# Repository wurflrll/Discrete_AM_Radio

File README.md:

# Discrete AM Radio

## 27MHz AM Radio from Discrete Components

# Descriptions
This project comprises two different PCBs, a Receiver and Transmitter.  The circuits rely on basic BJT amplifier designs, a 27MHz oscillator.

## Added Files
This contains all the files from my two KiCad project and the BOMS (factory assembled unlike Sawtooth generator project).

## Problems
Crystal Oscillator has issues because the loop gain is too high, due to a mispredicted Q factor of
the crystal.

Trying to use a simple op-amp circuit for the preamplification of the microphone signal was a bad idea.  
The NCS20072D is simply too high noise, especially for a high gain pre-amp from a ~-50dB microphone.

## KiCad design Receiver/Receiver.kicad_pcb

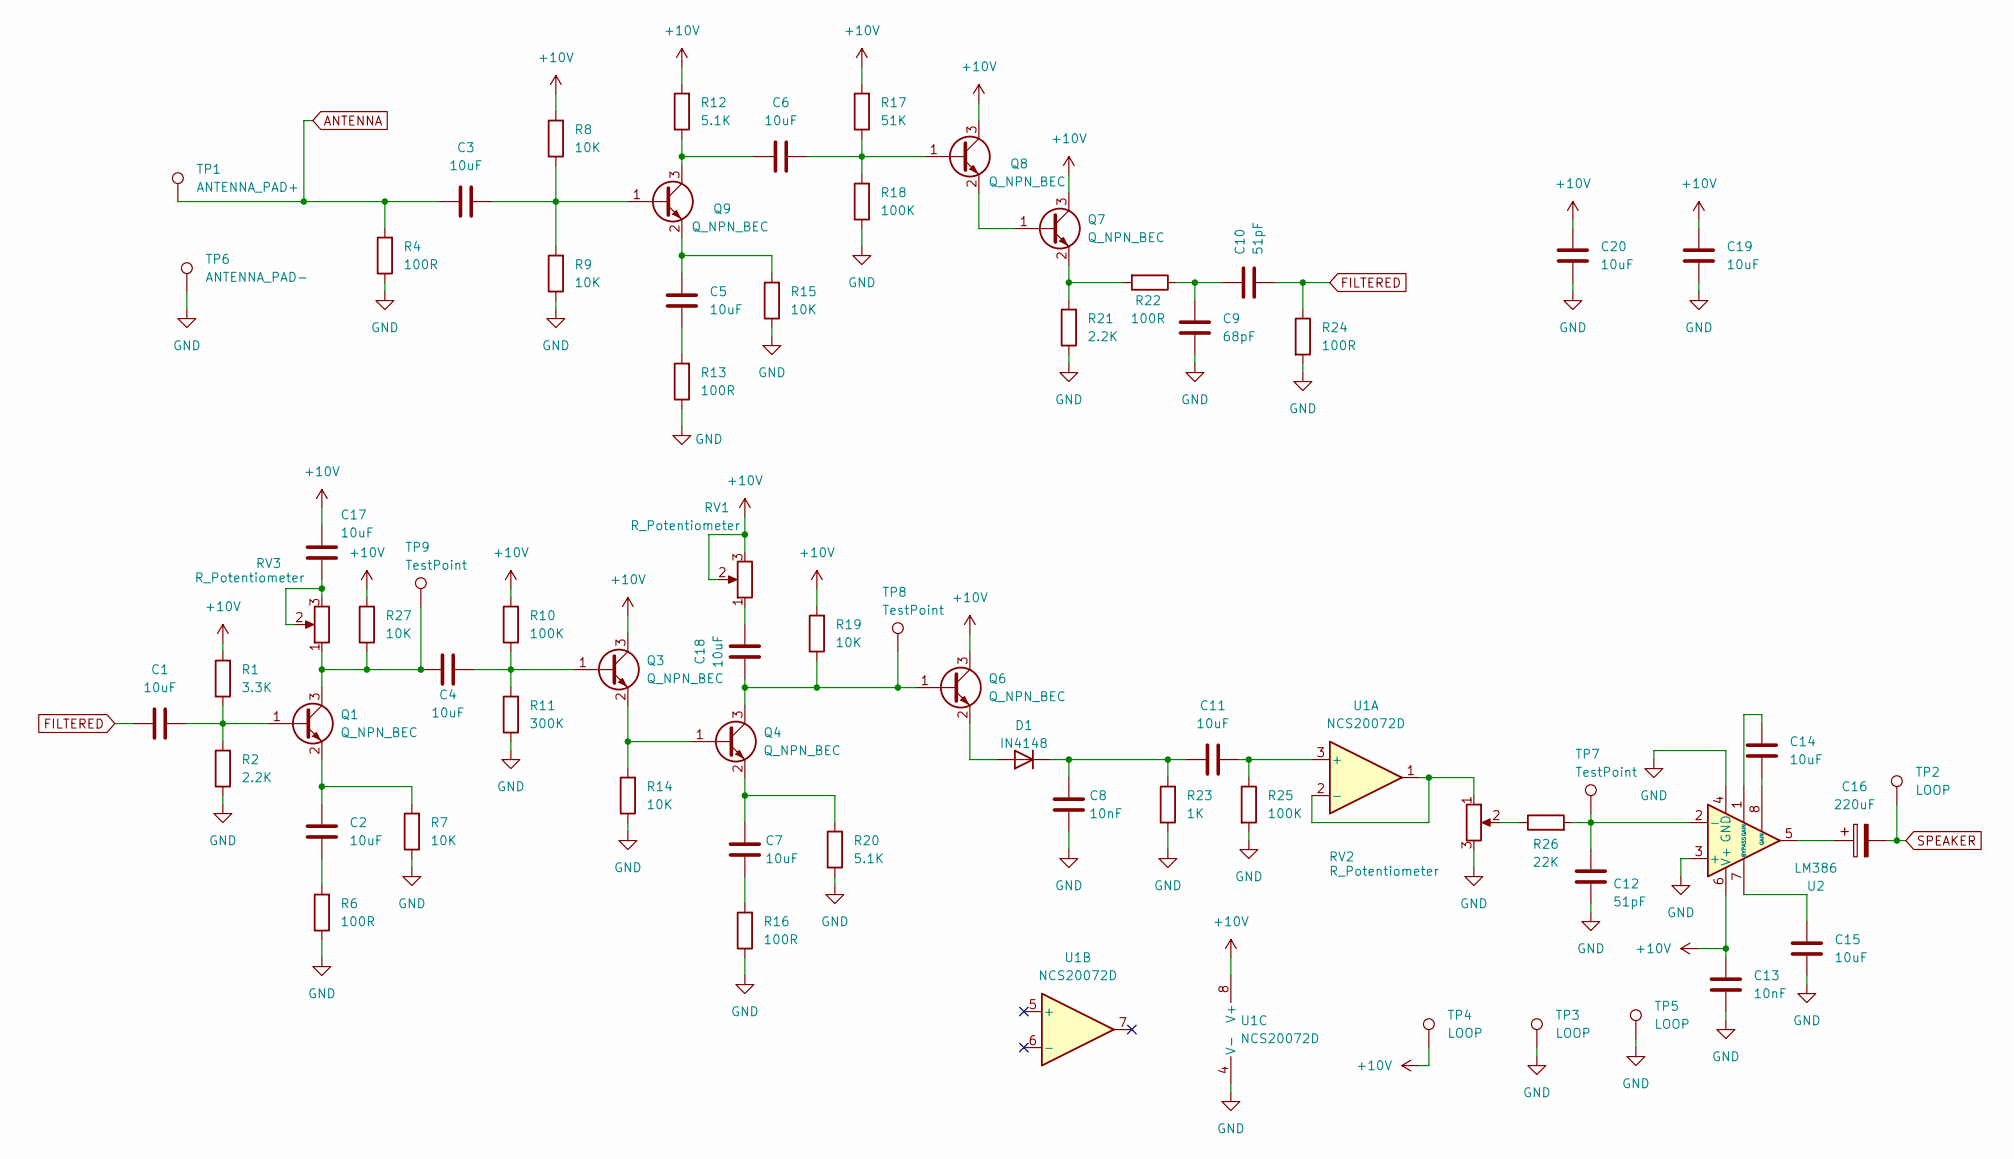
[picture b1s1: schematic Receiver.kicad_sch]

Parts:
C1, C2, C3, C4, C5, C6, C7, C11, C14, C15, C17, C18, C19, C20: 10uF; C_0603_1608Metric
C8, C13: 10nF; C_0603_1608Metric
C9: 68pF; C_0603_1608Metric
C10, C12: 51pF; C_0603_1608Metric
C16: 220uF; C_Radial_D8.0mm_H11.5mm_P3.50mm
D1: IN4148; D_SOD-123
Q1, Q3, Q4, Q6, Q7, Q8, Q9: Q_NPN_BEC; SOT-23
R1: 3.3K; R_0603_1608Metric
R2, R21: 2.2K; R_0603_1608Metric
R4, R6, R13, R16, R22, R24: 100R; R_0603_1608Metric
R7, R8, R9, R14, R15, R19, R27: 10K; R_0603_1608Metric
R10, R18, R25: 100K; R_0603_1608Metric
R11: 300K; R_0603_1608Metric
R12, R20: 5.1K; R_0603_1608Metric
R17: 51K; R_0603_1608Metric
R23: 1K; R_0603_1608Metric
R26: 22K; R_0603_1608Metric
RV1, RV2, RV3: R_Potentiometer; Potentiometer_Bourns_3386P_Vertical
TP1: ANTENNA_PAD+; TestPoint_Pad_D4.0mm
TP2, TP3, TP4, TP5: LOOP; TestPoint_Loop_D2.50mm_Drill1.0mm
TP6: ANTENNA_PAD-; TestPoint_Pad_D4.0mm
TP7, TP8, TP9: TestPoint; TestPoint_Plated_Hole_D2.0mm
U1: NCS20072D; SOIC-8_3.9x4.9mm_P1.27mm
U2: LM386; SOIC-8_3.9x4.9mm_P1.27mm

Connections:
+10V: C13.1, C17.2, C19.2, C20.2, Q3.3 (C), Q6.3 (C), Q7.3 (C), Q8.3 (C), R1.2, R8.2, R10.2, R12.2, R17.2, R19.2, R27.2, RV1.2, RV1.3, TP4.1, U1.8 (V+), U2.6 (V+)
ANTENNA: C3.1, R4.2, TP1.1
FILTERED: C1.1, C10.2, R24.1
GND: C8.1, C9.2, C12.2, C13.2, C15.1, C19.1, C20.1, R2.1, R4.1, R6.1, R7.1, R9.1, R11.1, R13.1, R14.1, R15.1, R16.1, R18.1, R20.1, R21.1, R23.1, R24.2, R25.2, RV2.3, TP3.1, TP5.1, TP6.1, U1.4 (V-), U2.3 (+), U2.4 (GND)
unnamed: C2.1, R6.2
unnamed: C5.1, R13.2
unnamed: C7.1, R16.2
unnamed: C9.1, C10.1, R22.1
unnamed: C14.1, U2.8 (GAIN)
unnamed: C14.2, U2.1 (GAIN)
unnamed: C16.1, U2.5
unnamed: C17.1, RV3.2, RV3.3
unnamed: C18.1, RV1.1
unnamed: D1.2 (A), Q6.2 (E)
unnamed: C8.2, C11.1, D1.1 (K), R23.2
unnamed: C1.2, Q1.1 (B), R1.1, R2.2
unnamed: C4.2, Q1.3 (C), R27.1, RV3.1, TP9.1
unnamed: C2.2, Q1.2 (E), R7.2
unnamed: C4.1, Q3.1 (B), R10.1, R11.2
unnamed: Q3.2 (E), Q4.1 (B), R14.2
unnamed: C18.2, Q4.3 (C), Q6.1 (B), R19.1, TP8.1
unnamed: C7.2, Q4.2 (E), R20.2
unnamed: Q7.1 (B), Q8.2 (E)
unnamed: Q7.2 (E), R21.2, R22.2
unnamed: C6.1, Q8.1 (B), R17.1, R18.2
unnamed: C3.2, Q9.1 (B), R8.1, R9.2
unnamed: C6.2, Q9.3 (C), R12.1
unnamed: C5.2, Q9.2 (E), R15.2
unnamed: R26.1, RV2.2
unnamed: C11.2, R25.1, U1.3 (+)
unnamed: RV2.1, U1.1, U1.2 (-)
unnamed: C12.1, R26.2, TP7.1, U2.2 (-)
unnamed: C15.2, U2.7 (BYPASS)
SPEAKER: C16.2, TP2.1

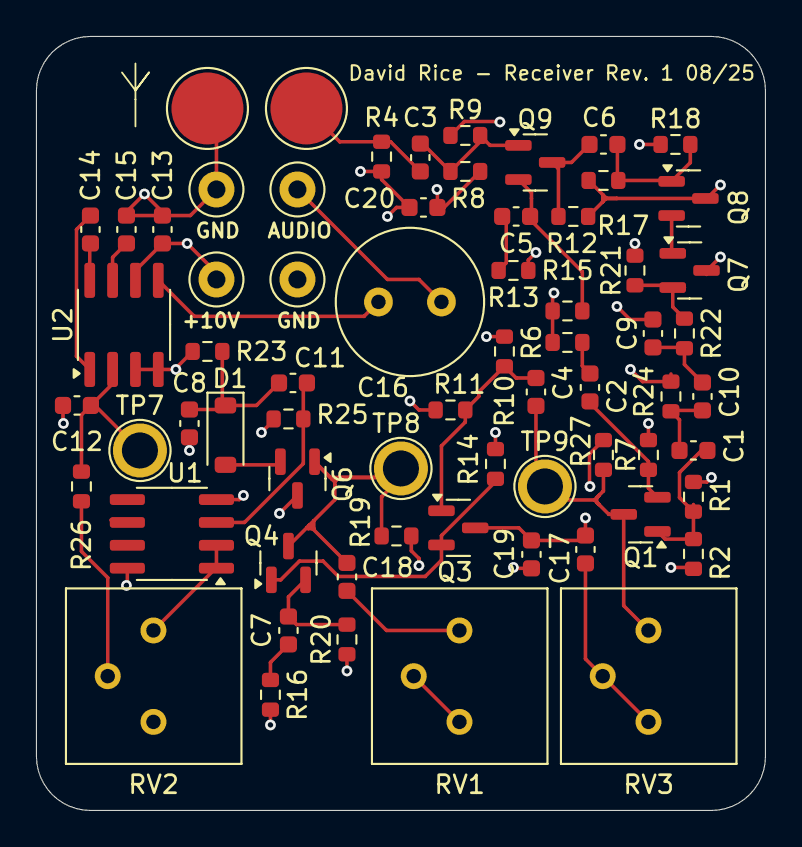
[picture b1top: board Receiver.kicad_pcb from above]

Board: 2 copper layers, 40.5 x 43.0 mm, 67 parts (0 on the bottom side), 34 nets.

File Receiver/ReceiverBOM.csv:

Id,Designator,Footprint,Quantity,Designation,Supplier and ref
1,"R2,R21",R_0603_1608Metric,2,2.2K,C114662
2,"R12,R20",R_0603_1608Metric,2,5.1K,C105580
3,C16,C_Radial_D8.0mm_H11.5mm_P3.50mm,1,220uF,C107639
4,"C20,C3,C17,C19,C5,C11,C15,C2,C1,C6,C4,C14,C18,C7",C_0603_1608Metric,14,10uF,C19702
5,"RV2,RV3,RV1",Potentiometer_Bourns_3386P_Vertical,3,R_Potentiometer,C48642119
6,"R6,R24,R16,R13,R22,R4",R_0603_1608Metric,6,100R,C105588
7,"C10,C12",C_0603_1608Metric,2,51pF,C107051
8,"R14,R15,R7,R9,R27,R8",R_0603_1608Metric,6,10K,C98220
9,"Q3,Q6,Q7,Q8,Q4,Q1,Q9",SOT-23,7,Q_NPN_BEC,C3199172
10,"R18,R25",R_0603_1608Metric,2,100K,C14675
11,"R19,R1",R_0603_1608Metric,2,3.16K,C2930087
12,"C8,C13",C_0603_1608Metric,2,10nF,C100042
13,R26,R_0603_1608Metric,1,22K,C31850
14,R11,R_0603_1608Metric,1,332K,C4351218
15,R17,R_0603_1608Metric,1,51K,C107231
16,U2,SOIC-8_3.9x4.9mm_P1.27mm,1,LM386,C23573
17,R10,R_0603_1608Metric,1,110K,C2906984
18,"TP3,TP2,TP4,TP5",TestPoint_Loop_D2.50mm_Drill1.0mm,4,LOOP,C5199815
19,C9,C_0603_1608Metric,1,68pF,C62782
20,L1,L_Axial_L12.0mm_D5.0mm_P15.24mm_Horizontal_Fastron_MISC,1,4.7mH,C2931871
21,R23,R_0603_1608Metric,1,1K,C22548
22,U1,SOIC-8_3.9x4.9mm_P1.27mm,1,NCS20072D,C89845
23,D1,D_SOD-123,1,IN4148,C82544

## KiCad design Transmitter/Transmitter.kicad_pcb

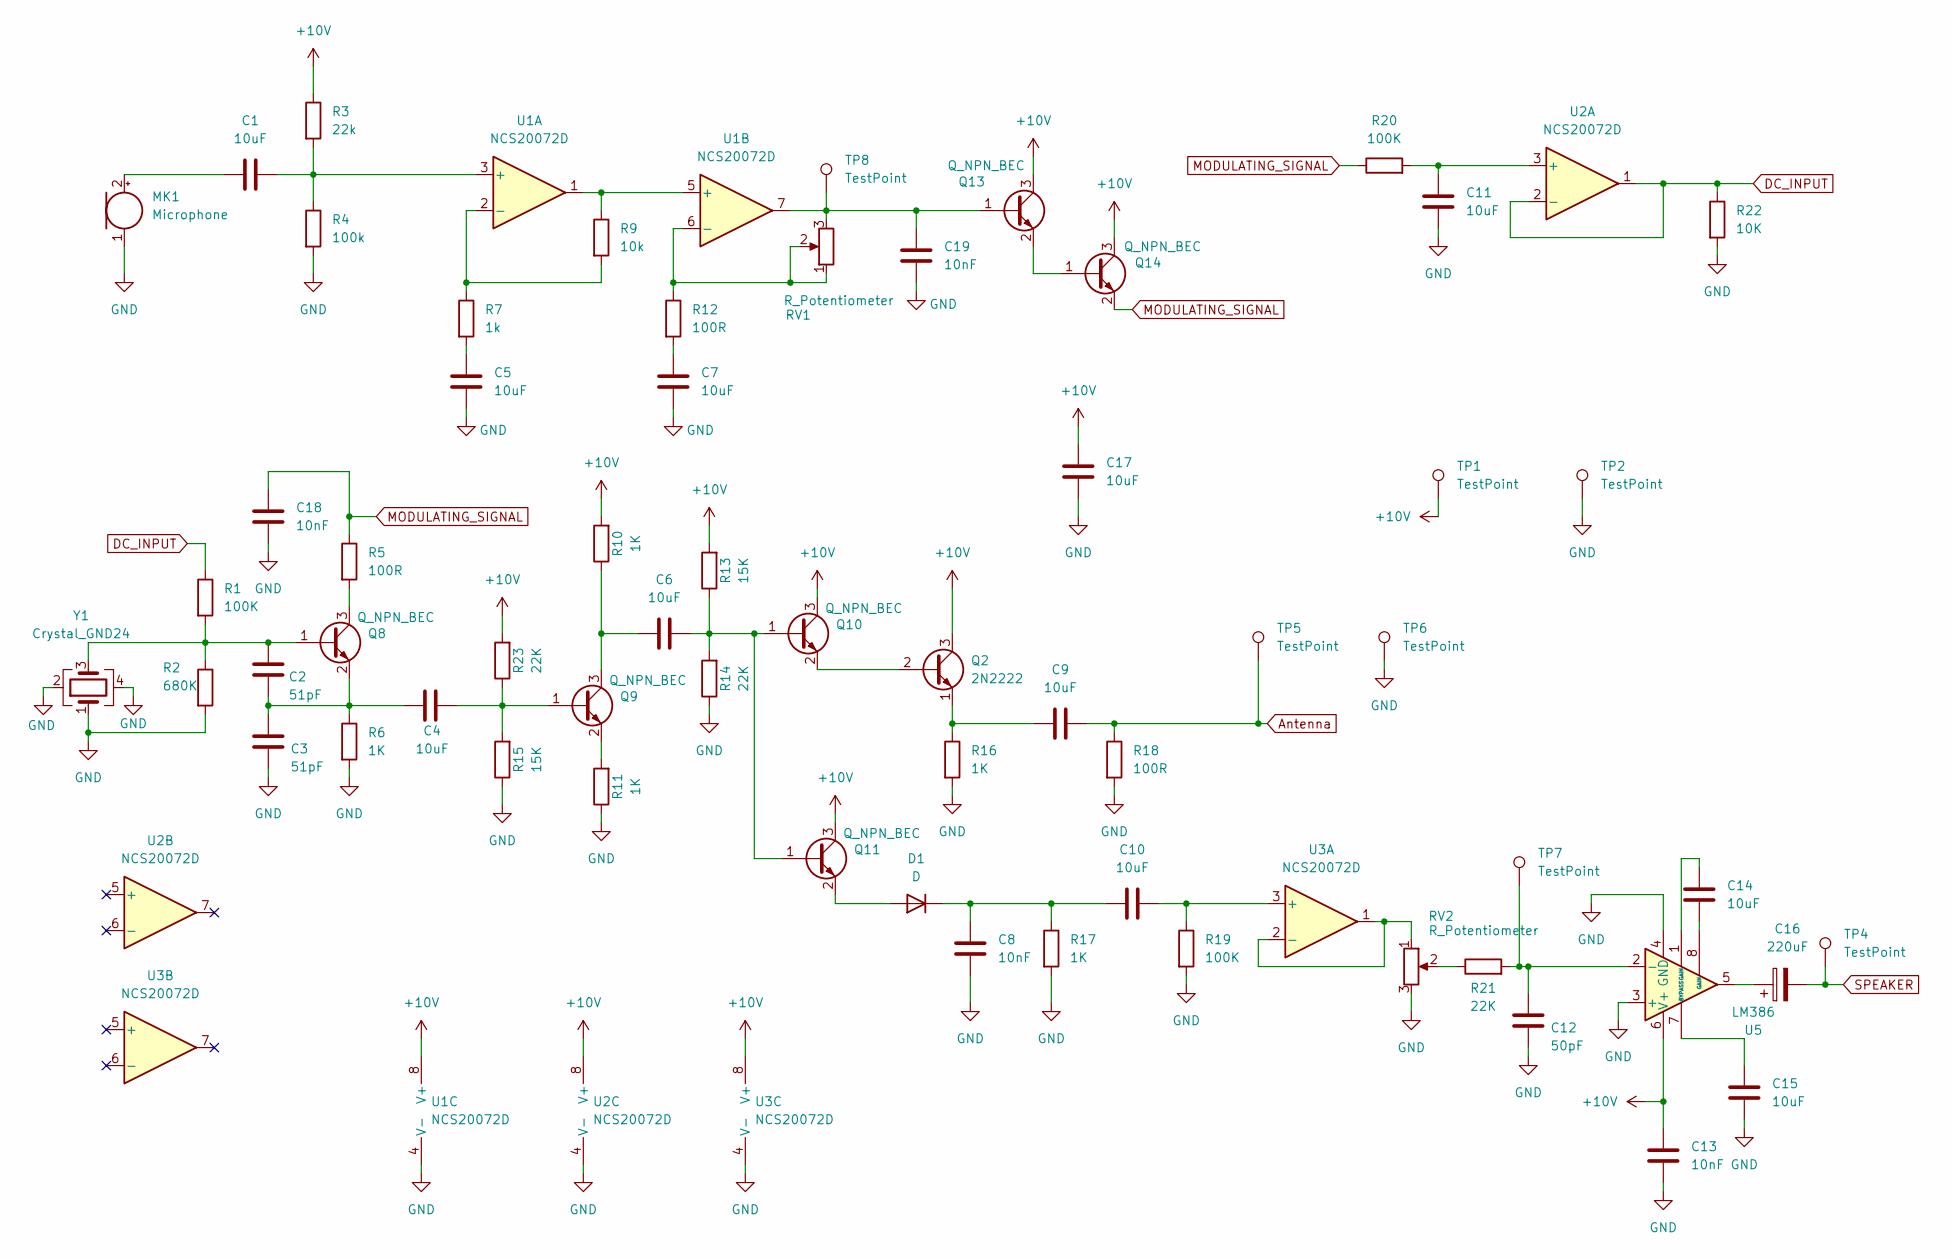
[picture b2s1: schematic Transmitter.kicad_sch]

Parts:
C1, C4, C5, C6, C7, C9, C10, C11, C14, C15, C17: 10uF; C_0603_1608Metric
C2, C3: 51pF; C_0603_1608Metric
C8, C13, C18, C19: 10nF; C_0603_1608Metric
C12: 50pF; C_0603_1608Metric
C16: 220uF; C_Radial_D8.0mm_H11.5mm_P3.50mm
D1: D; D_SOD-123
MK1: Microphone; POM-2244P-C3310-2-R
Q2: 2N2222; TO-92
Q8, Q9, Q10, Q11, Q13, Q14: Q_NPN_BEC; SOT-23
R1, R19, R20: 100K; R_0603_1608Metric
R2: 680K; R_0603_1608Metric
R3: 22k; R_0603_1608Metric
R4: 100k; R_0603_1608Metric
R5, R12, R18: 100R; R_0603_1608Metric
R6, R10, R11, R16, R17: 1K; R_0603_1608Metric
R7: 1k; R_0603_1608Metric
R9: 10k; R_0603_1608Metric
R13, R15: 15K; R_0603_1608Metric
R14, R21, R23: 22K; R_0603_1608Metric
R22: 10K; R_0603_1608Metric
RV1, RV2: R_Potentiometer; Potentiometer_Bourns_3386P_Vertical
TP1, TP2, TP4: TestPoint; TestPoint_Loop_D2.50mm_Drill1.0mm
TP5, TP6: TestPoint; TestPoint_Pad_D4.0mm
TP7, TP8: TestPoint; TestPoint_Plated_Hole_D2.0mm
U1, U2, U3: NCS20072D; SOIC-8_3.9x4.9mm_P1.27mm
U5: LM386; SOIC-8_3.9x4.9mm_P1.27mm
Y1: Crystal_GND24; Crystal_SMD_SeikoEpson_TSX3225-4Pin_3.2x2.5mm

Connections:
+10V: C13.1, C17.2, Q2.3 (C), Q10.3 (C), Q11.3 (C), Q13.3 (C), Q14.3 (C), R3.1, R10.2, R13.2, R23.2, TP1.1, U1.8 (V+), U2.8 (V+), U3.8 (V+), U5.6 (V+)
Antenna: C9.2, R18.1, TP5.1
DC_INPUT: R1.1, R22.1, U2.1, U2.2 (-)
GND: C3.2, C5.2, C7.2, C8.2, C11.2, C12.2, C13.2, C15.1, C17.1, C18.2, C19.2, MK1.1 (-), R2.2, R4.2, R6.2, R11.1, R14.1, R15.1, R16.2, R17.2, R18.2, R19.2, R22.2, RV2.3, TP2.1, TP6.1, U1.4 (V-), U2.4 (V-), U3.4 (V-), U5.3 (+), U5.4 (GND), Y1.1, Y1.2, Y1.4
MODULATING_SIGNAL: C18.1, Q14.2 (E), R5.1, R20.1
unnamed: C5.1, R7.2
unnamed: C7.1, R12.2
unnamed: C14.1, U5.8 (GAIN)
unnamed: C14.2, U5.1 (GAIN)
unnamed: C16.1, U5.5
unnamed: D1.2 (A), Q11.2 (E)
unnamed: C8.1, C10.1, D1.1 (K), R17.1
unnamed: C1.1, MK1.2 (+)
unnamed: C9.1, Q2.1 (E), R16.1
unnamed: C2.1, Q8.1 (B), R1.2, R2.1, Y1.3
unnamed: Q8.3 (C), R5.2
unnamed: C2.2, C3.1, C4.2, Q8.2 (E), R6.1
unnamed: C4.1, Q9.1 (B), R15.2, R23.1
unnamed: C6.2, Q9.3 (C), R10.1
unnamed: Q9.2 (E), R11.2
unnamed: C6.1, Q10.1 (B), Q11.1 (B), R13.1, R14.2
unnamed: Q2.2 (B), Q10.2 (E)
unnamed: C19.1, Q13.1 (B), RV1.3, TP8.1, U1.7
unnamed: Q13.2 (E), Q14.1 (B)
unnamed: R21.1, RV2.2
unnamed: C1.2, R3.2, R4.1, U1.3 (+)
unnamed: R7.1, R9.2, U1.2 (-)
unnamed: R9.1, U1.1, U1.5 (+)
unnamed: R12.1, RV1.1, RV1.2, U1.6 (-)
unnamed: C11.1, R20.2, U2.3 (+)
unnamed: C10.2, R19.1, U3.3 (+)
unnamed: RV2.1, U3.1, U3.2 (-)
unnamed: C12.1, R21.2, TP7.1, U5.2 (-)
unnamed: C15.2, U5.7 (BYPASS)
SPEAKER: C16.2, TP4.1

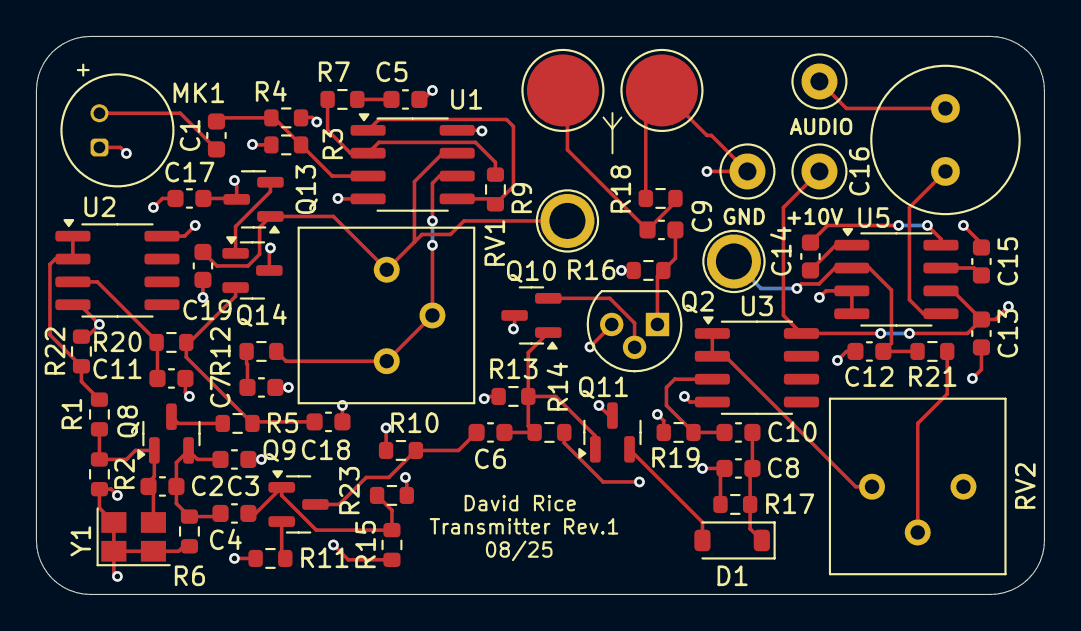
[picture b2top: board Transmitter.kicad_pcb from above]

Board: 2 copper layers, 56.0 x 31.0 mm, 64 parts (0 on the bottom side), 35 nets.

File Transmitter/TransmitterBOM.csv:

Designator,Footprint,Quantity,Value,LCSC Part #
C1,603,1,10u,C19702
"C10, C11, C14, C15, C17, C4, C5, C6, C7, C9",603,10,10uF,C19702
C12,603,1,50pF,C107231
"C13, C18, C19, C8",603,4,10nF,C100042
C16,C_Radial_D8.0mm_H11.5mm_P3.50mm,1,220uF,C107639
"C2, C3",603,2,51pF,C107231
D1,D_SOD-123,1,D,C83528
MK1,POM-2244P-C3310-2-R,1,Microphone,C20200111
"Q10, Q11, Q13, Q14, Q8, Q9",SOT-23,6,Q_NPN_BEC,C3199172
Q2,TO-92,1,2N2222,C118536
R1,603,1,110K,C14675
"R10, R11, R16, R17, R6, R7",603,6,1K,C22548
"R12, R18, R5",603,3,100R,C105588
"R13, R15",603,2,15K,C114661
"R14, R21, R23, R3",603,4,22K,C31850
"R19, R20, R4",603,3,100K,C14675
R2,603,1,680K,C137690
"R22, R9",603,2,10K,C98220
"RV1, RV2",Potentiometer_Bourns_3386P_Vertical,2,R_Potentiometer,
"TP1, TP2, TP4",TestPoint_Loop_D2.50mm_Drill1.0mm,3,TestPoint,
"TP5, TP6",TestPoint_Pad_D4.0mm,2,TestPoint,
"TP7, TP8",TestPoint_Plated_Hole_D2.0mm,2,TestPoint,
"U1, U2, U3",SOIC-8_3.9x4.9mm_P1.27mm,3,NCS20072D,C89845
U5,SOIC-8_3.9x4.9mm_P1.27mm,1,LM386,C23573
Y1,Crystal_SMD_SeikoEpson_TSX3225-4Pin_3.2x2.5mm,1,Crystal_GND24,C37635384

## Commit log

2025-08-22 Initial Committing Files
